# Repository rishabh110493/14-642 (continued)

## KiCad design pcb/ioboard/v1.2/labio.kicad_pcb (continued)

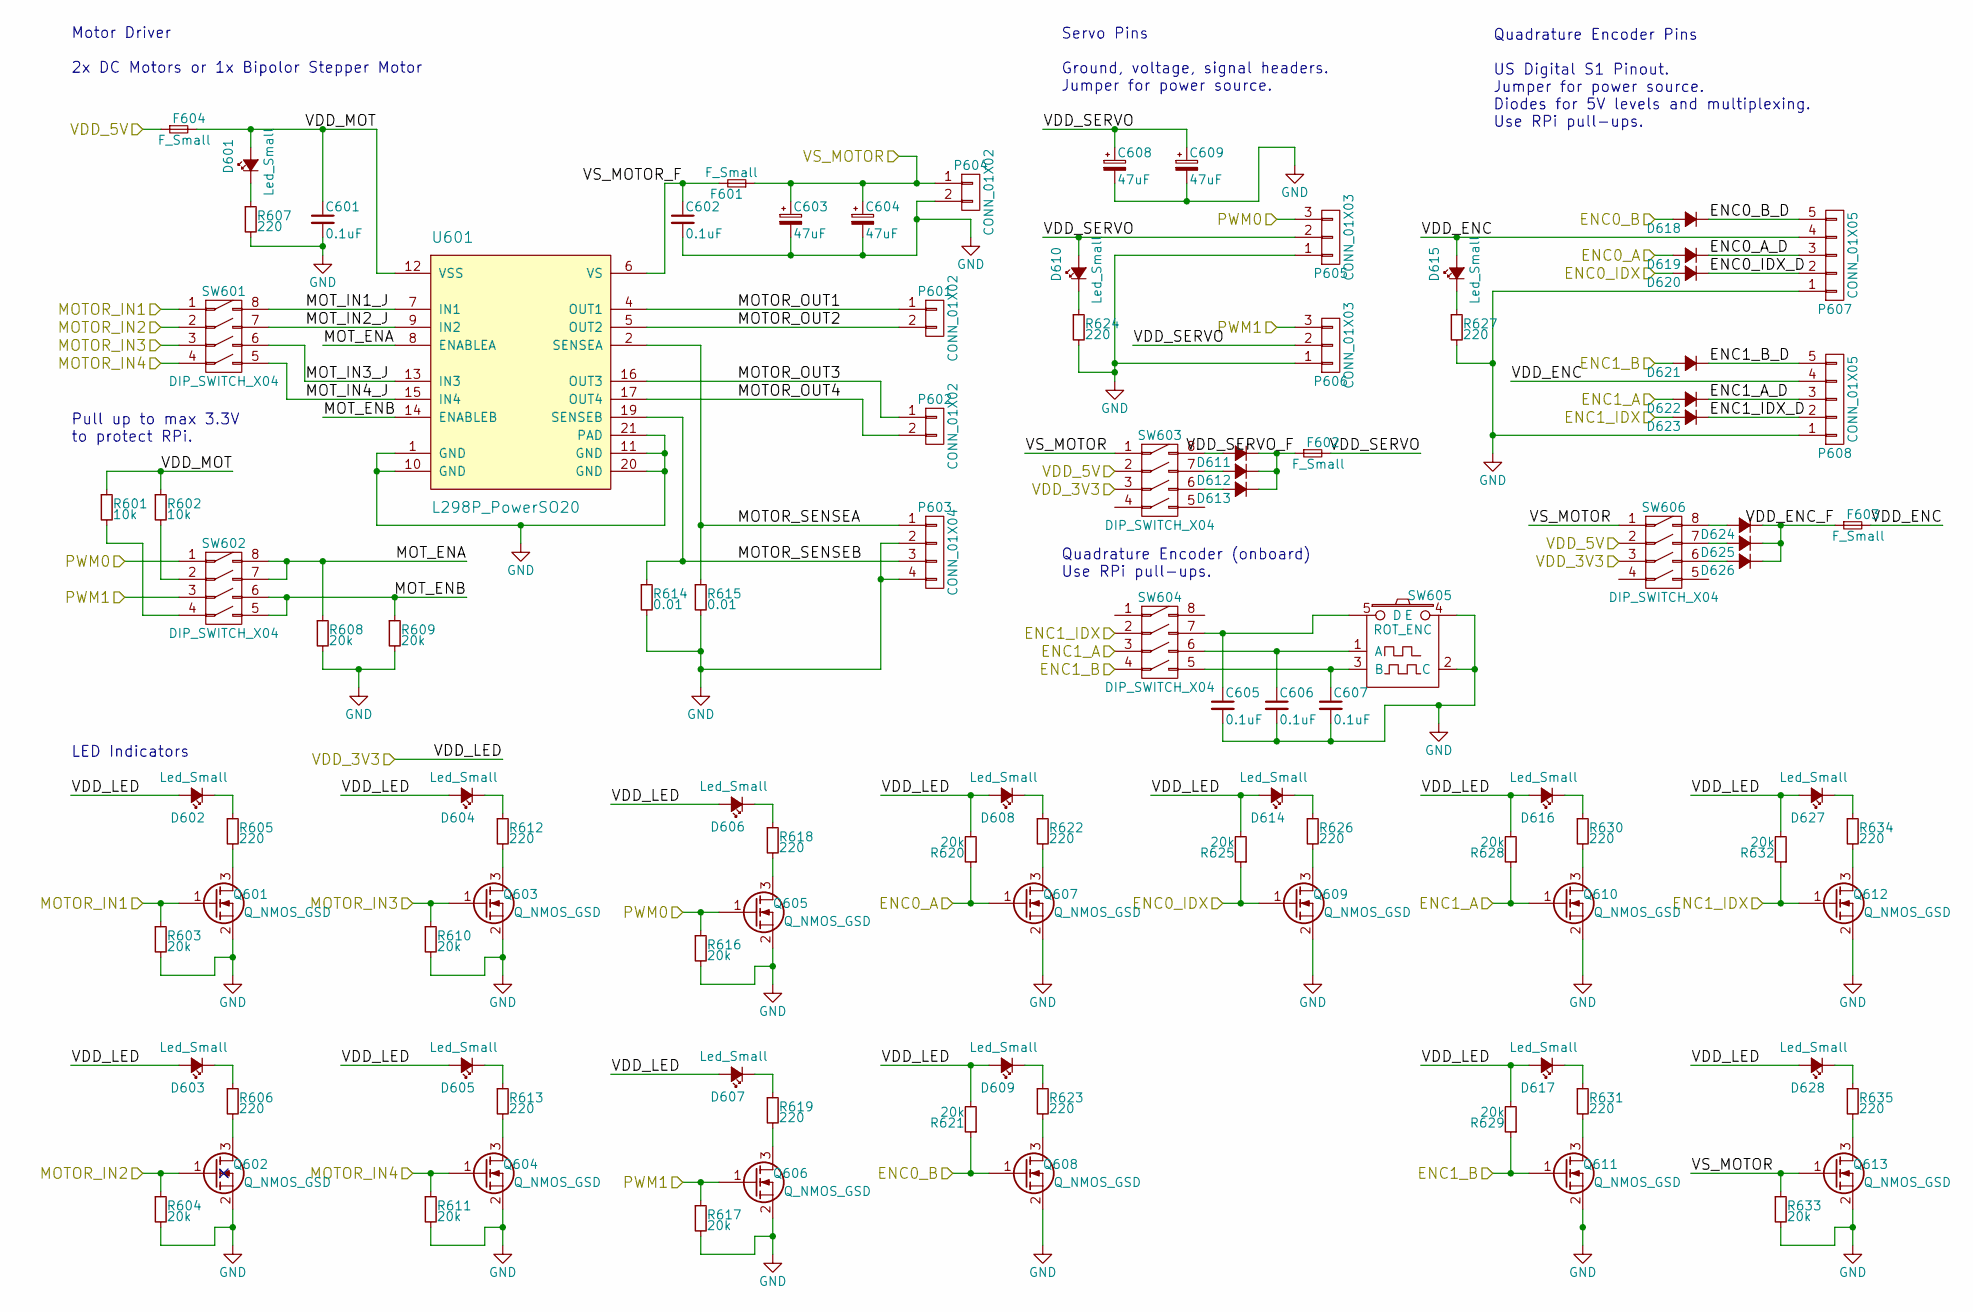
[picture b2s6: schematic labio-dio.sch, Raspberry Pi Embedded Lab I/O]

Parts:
C601, C602, C605, C606, C607: 0.1uF; C_0603
C603, C604, C608, C609: 47uF; c_elec_6.3x5.8
D601, D602, D603, D604, D605, D606, D607, D608, D609, D610, D614, D615, D616, D617, D627, D628: Led_Small; LED-0603
D611, D612, D613, D618, D619, D620, D621, D622, D623, D624, D625, D626: D_Small; SOD-523
F601: F_Small; OMNI-BLOCK_Fuse_10x5mm_Littelfuse
F602, F603, F604: F_Small; R_1206
P601, P602, P604: CONN_01X02; Pin_Header_Straight_1x02_Pitch3.5mm
P603: CONN_01X04; Pin_Header_Straight_1x04
P605, P606: CONN_01X03; Pin_Header_Straight_1x03
P607, P608: CONN_01X05; Pin_Header_Straight_1x05
Q601, Q602, Q603, Q604, Q605, Q606, Q607, Q608, Q609, Q610, Q611, Q612, Q613: Q_NMOS_GSD; SOT-23
R601, R602: 10k; R_0603
R603, R604, R608, R609, R610, R611, R616, R617, R620, R621, R625, R628, R629, R632, R633: 20k; R_0603
R605, R606, R607, R612, R613, R618, R619, R622, R623, R624, R626, R627, R630, R631, R634, R635: 220; R_0603
R614, R615: 0.01; R_1206
SW601, SW602, SW603, SW604, SW606: DIP_SWITCH_X04; DIP-8_W7.62mm_SMT
SW605: ROT_ENC; Rot-Enc-12mm-Horiz-Button
U601: L298P_PowerSO20; PowerSO20

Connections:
/3V3_EXTRA: D602.2 (A), D603.2 (A), D604.2 (A), D605.2 (A), D606.2 (A), D607.2 (A), D608.2 (A), D609.2 (A), D614.2 (A), D616.2 (A), D617.2 (A), D627.2 (A), D628.2 (A), R620.2, R621.2, R625.2, R628.2, R629.2, R632.2, SW603.3 (3A), SW606.3 (3A); also elsewhere on the board
/5V: F604.1, SW603.2 (2A), SW606.2 (2A); also elsewhere on the board
/I2C_INT: D619.2 (A), Q607.1 (G), R620.1; also elsewhere on the board
/I2S_BCLK: Q604.1 (G), R611.1, SW601.4 (4A); also elsewhere on the board
/I2S_LRCLK: Q603.1 (G), R610.1, SW601.3 (3A); also elsewhere on the board
/I2S_SDIN: Q601.1 (G), R603.1, SW601.1 (1A); also elsewhere on the board
/I2S_SDOUT: Q602.1 (G), R604.1, SW601.2 (2A); also elsewhere on the board
/PWM0: P605.3, Q605.1 (G), R616.1, SW602.1 (1A); also elsewhere on the board
/PWM1: P606.3, Q606.1 (G), R617.1, SW602.3 (3A); also elsewhere on the board
/labio-dio/ENC0_A_D: D619.1 (K), P607.3
/labio-dio/ENC0_B_D: D618.1 (K), P607.5
/labio-dio/ENC0_IDX_D: D620.1 (K), P607.2
/labio-dio/ENC1_A_D: D622.1 (K), P608.3
/labio-dio/ENC1_B_D: D621.1 (K), P608.5
/labio-dio/ENC1_IDX_D: D623.1 (K), P608.2
/labio-dio/MOTOR_OUT1: P601.1, U601.4 (OUT1)
/labio-dio/MOTOR_OUT2: P601.2, U601.5 (OUT2)
/labio-dio/MOTOR_OUT3: P602.1, U601.16 (OUT3)
/labio-dio/MOTOR_OUT4: P602.2, U601.17 (OUT4)
/labio-dio/MOTOR_SENSEA: P603.1, R615.1, U601.2 (SENSEA)
/labio-dio/MOTOR_SENSEB: P603.3, R614.1, U601.19 (SENSEB)
/labio-dio/MOT_ENA: R608.1, SW602.7 (2A), SW602.8 (1B), U601.8 (ENABLEA)
/labio-dio/MOT_ENB: R609.1, SW602.5 (4B), SW602.6 (3B), U601.14 (ENABLEB)
/labio-dio/MOT_IN1_J: SW601.8 (1B), U601.7 (IN1)
/labio-dio/MOT_IN2_J: SW601.7 (2A), U601.9 (IN2)
/labio-dio/MOT_IN3_J: SW601.6 (3B), U601.13 (IN3)
/labio-dio/MOT_IN4_J: SW601.5 (4B), U601.15 (IN4)
/labio-dio/VDD_ENC: D615.2 (A), F603.2, P607.4, P608.4
/labio-dio/VDD_ENC_F: D624.1 (K), D625.1 (K), D626.1 (K), F603.1
/labio-dio/VDD_MOT: C601.1, D601.2 (A), F604.2, R601.1, R602.1, U601.12 (VSS)
/labio-dio/VDD_SERVO: C608.1, C609.1, D610.2 (A), F602.2, P605.2, P606.2
/labio-dio/VDD_SERVO_F: D611.1 (K), D612.1 (K), D613.1 (K), F602.1
/labio-dio/VS_MOTOR: C603.1, C604.1, F601.1, P604.1, Q613.1 (G), R633.1, SW603.1 (1A), SW606.1 (1A); also elsewhere on the board
/labio-dio/VS_MOTOR_F: C602.1, F601.2, U601.6 (VS)
/labio-dpad/DPAD_CENTER: D622.2 (A), Q610.1 (G), R628.1, SW604.3 (3A); also elsewhere on the board
/labio-dpad/DPAD_DOWN: D623.2 (A), Q612.1 (G), R632.1, SW604.2 (2A); also elsewhere on the board
/labio-dpad/DPAD_LEFT: D618.2 (A), Q608.1 (G), R621.1; also elsewhere on the board
/labio-dpad/DPAD_RIGHT: D621.2 (A), Q611.1 (G), R629.1, SW604.4 (4A); also elsewhere on the board
/labio-dpad/DPAD_UP: D620.2 (A), Q609.1 (G), R625.1; also elsewhere on the board
GND: C601.2, C602.2, C603.2, C604.2, C605.2, C606.2, C607.2, C608.2, C609.2, P603.2, P603.4, P604.2, P605.1, P606.1, P607.1, P608.1, Q601.2 (S), Q602.2 (S), Q603.2 (S), Q604.2 (S), Q605.2 (S), Q606.2 (S), Q607.2 (S), Q608.2 (S), Q609.2 (S), Q610.2 (S), Q611.2 (S), Q612.2 (S), Q613.2 (S), R603.2, R604.2, R607.2, R608.2, R609.2, R610.2, R611.2, R614.2, R615.2, R616.2, R617.2, R624.2, R627.2, R633.2, SW605.2 (C), SW605.4 (E), U601.1 (GND), U601.10 (GND), U601.11 (GND), U601.20 (GND), U601.21 (PAD); also elsewhere on the board
unnamed: C605.1, SW604.7 (2A), SW605.5 (D)
unnamed: C606.1, SW604.6 (3B), SW605.1 (A)
unnamed: C607.1, SW604.5 (4B), SW605.3 (B)
unnamed: D601.1 (K), R607.1
unnamed: D602.1 (K), R605.1
unnamed: D603.1 (K), R606.1
unnamed: D604.1 (K), R612.1
unnamed: D605.1 (K), R613.1
unnamed: D606.1 (K), R618.1
unnamed: D607.1 (K), R619.1
unnamed: D608.1 (K), R622.1
unnamed: D609.1 (K), R623.1
unnamed: D610.1 (K), R624.1
unnamed: D611.2 (A), SW603.8 (1B)
unnamed: D612.2 (A), SW603.7 (2A)
unnamed: D613.2 (A), SW603.6 (3B)
unnamed: D614.1 (K), R626.1
unnamed: D615.1 (K), R627.1
unnamed: D616.1 (K), R630.1
unnamed: D617.1 (K), R631.1
unnamed: D624.2 (A), SW606.8 (1B)
unnamed: D625.2 (A), SW606.7 (2A)
unnamed: D626.2 (A), SW606.6 (3B)
unnamed: D627.1 (K), R634.1
unnamed: D628.1 (K), R635.1
unnamed: Q601.3 (D), R605.2
unnamed: Q602.3 (D), R606.2
unnamed: Q603.3 (D), R612.2
unnamed: Q604.3 (D), R613.2
unnamed: Q605.3 (D), R618.2
unnamed: Q606.3 (D), R619.2
unnamed: Q607.3 (D), R622.2
unnamed: Q608.3 (D), R623.2
unnamed: Q609.3 (D), R626.2
unnamed: Q610.3 (D), R630.2
unnamed: Q611.3 (D), R631.2
unnamed: Q612.3 (D), R634.2
unnamed: Q613.3 (D), R635.2
unnamed: R601.2, SW602.4 (4A)
unnamed: R602.2, SW602.2 (2A)

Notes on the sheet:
Quadrature Encoder Pins US Digital S1 Pinout. Jumper for power source. Diodes for 5V levels and multiplexing. Use RPi pull-ups.
Servo Pins Ground, voltage, signal headers. Jumper for power source.
Motor Driver 2x DC Motors or 1x Bipolor Stepper Motor
LED Indicators
Quadrature Encoder (onboard) Use RPi pull-ups.
Pull up to max 3.3V to protect RPi.

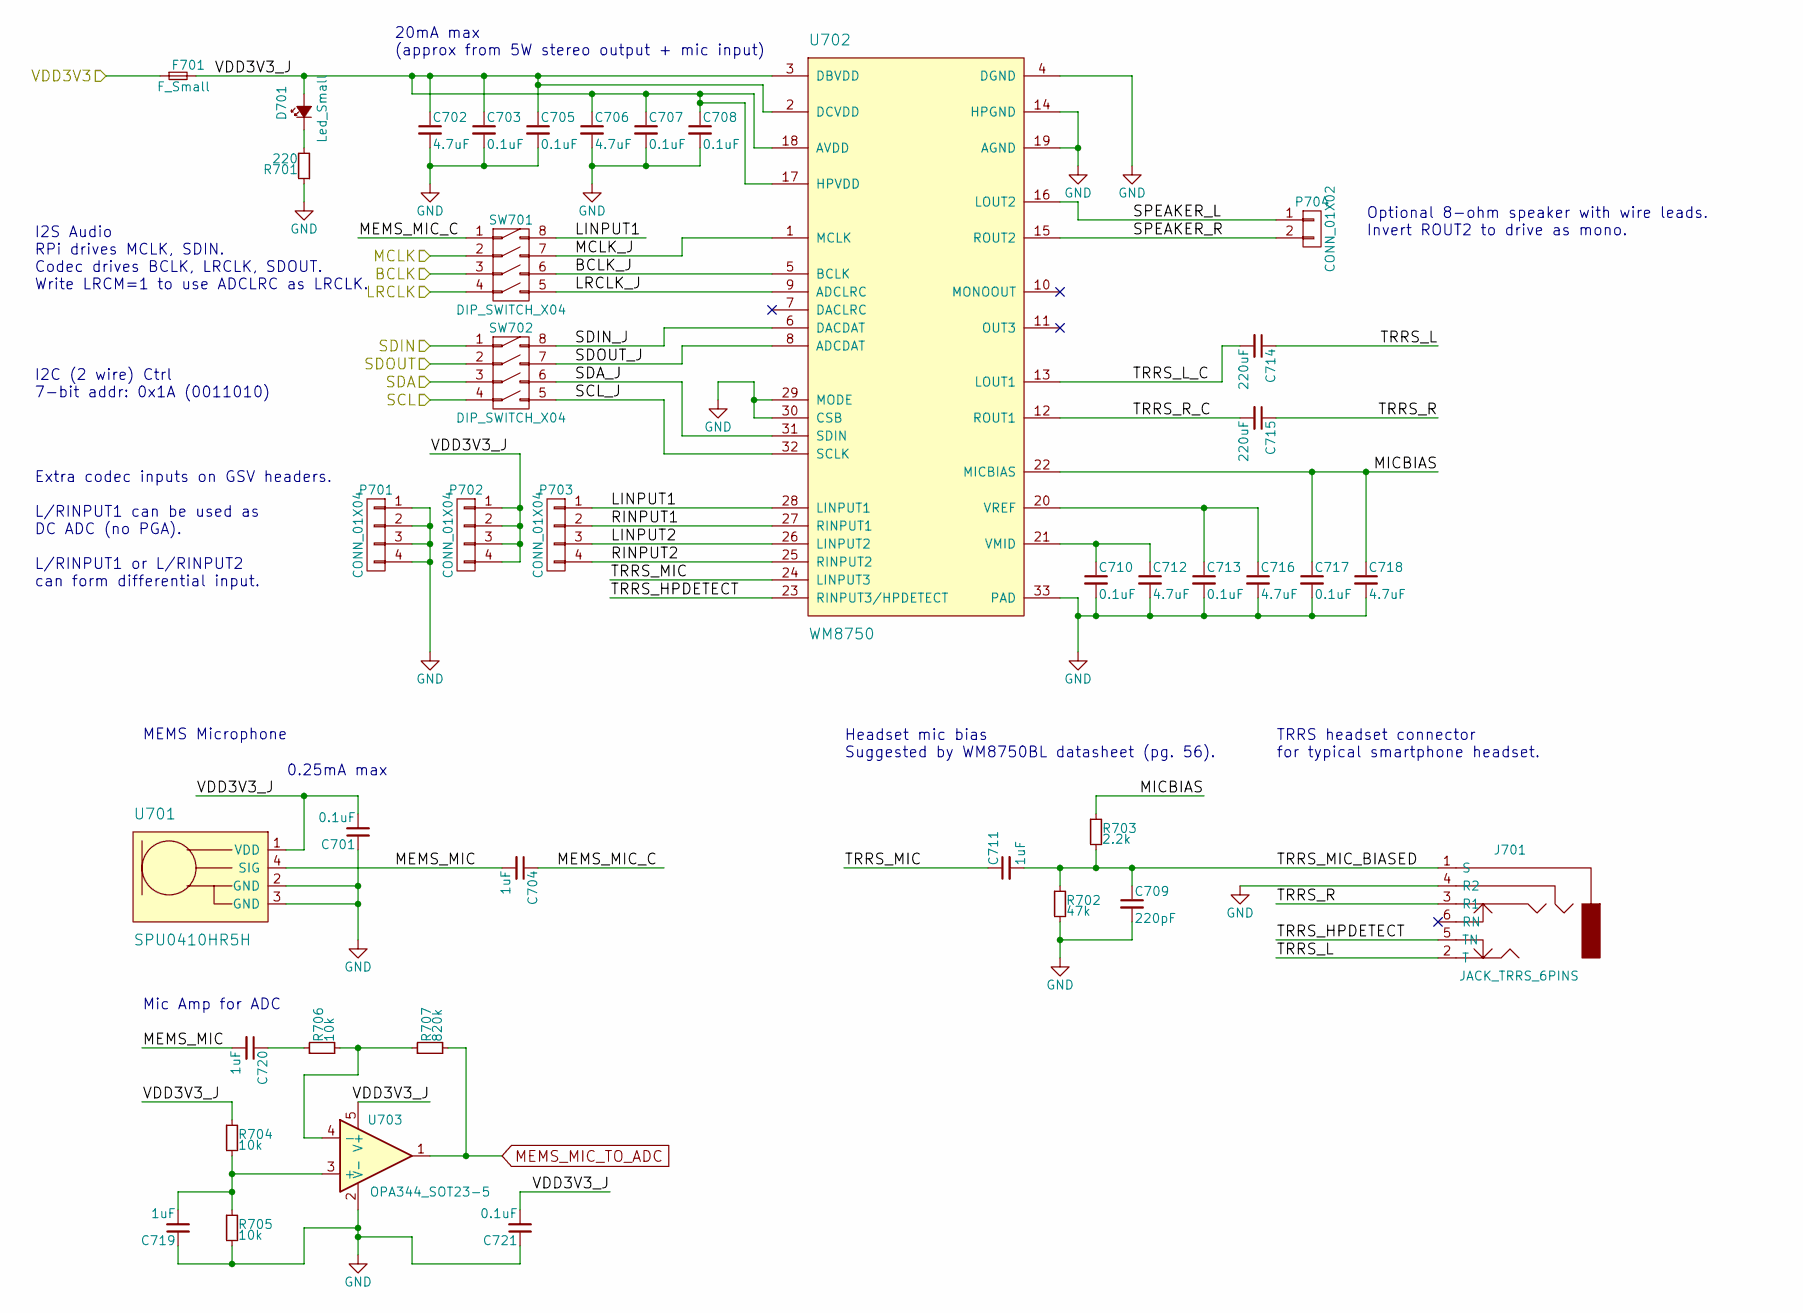
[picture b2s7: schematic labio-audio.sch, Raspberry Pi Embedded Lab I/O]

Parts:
C701, C703, C705, C707, C708, C710, C713, C717, C721: 0.1uF; C_0603
C702, C706, C712, C716, C718: 4.7uF; C_0805
C704, C711, C719, C720: 1uF; C_0603
C709: 220pF; C_0603
C714, C715: 220uF; C_1210
D701: Led_Small; LED-0603
F701: F_Small; R_1206
J701: JACK_TRRS_6PINS; 3.5mm-Jack-CUI-SJ-4351X
P701, P702, P703: CONN_01X04; Pin_Header_Straight_1x04
P704: CONN_01X02; Pin_Header_Straight_1x02
R701: 220; R_0603
R702: 47k; R_0603
R703: 2.2k; R_0603
R704, R705, R706: 10k; R_0603
R707: 820k; R_0603
SW701, SW702: DIP_SWITCH_X04; DIP-8_W7.62mm_SMT
U701: SPU0410HR5H
U702: WM8750; QFN-32-1EP_5x5mm_Pitch0.5mm
U703: OPA344_SOT23-5; SOT-23-5

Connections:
/3V3_EXTRA: F701.1; also elsewhere on the board
/GPCLK1: SW701.2 (2A); also elsewhere on the board
/I2C_SCL: SW702.4 (4A); also elsewhere on the board
/I2C_SDA: SW702.3 (3A); also elsewhere on the board
/I2S_BCLK: SW701.3 (3A); also elsewhere on the board
/I2S_LRCLK: SW701.4 (4A); also elsewhere on the board
/I2S_SDIN: SW702.1 (1A); also elsewhere on the board
/I2S_SDOUT: SW702.2 (2A); also elsewhere on the board
/labio-audio/BCLK_J: SW701.6 (3B), U702.5 (BCLK)
/labio-audio/LINPUT1: P703.1, SW701.8 (1B), U702.28 (LINPUT1)
/labio-audio/LINPUT2: P703.3, U702.26 (LINPUT2)
/labio-audio/LRCLK_J: SW701.5 (4B), U702.9 (ADCLRC)
/labio-audio/MCLK_J: SW701.7 (2A), U702.1 (MCLK)
/labio-audio/MEMS_MIC: C704.2, C720.2, U701.4 (SIG)
/labio-audio/MEMS_MIC_C: C704.1, SW701.1 (1A)
/labio-audio/MICBIAS: C717.1, C718.1, R703.1, U702.22 (MICBIAS)
/labio-audio/RINPUT1: P703.2, U702.27 (RINPUT1)
/labio-audio/RINPUT2: P703.4, U702.25 (RINPUT2)
/labio-audio/SCL_J: SW702.5 (4B), U702.32 (SCLK)
/labio-audio/SDA_J: SW702.6 (3B), U702.31 (SDIN)
/labio-audio/SDIN_J: SW702.8 (1B), U702.6 (DACDAT)
/labio-audio/SDOUT_J: SW702.7 (2A), U702.8 (ADCDAT)
/labio-audio/SPEAKER_L: P704.1, U702.16 (LOUT2)
/labio-audio/SPEAKER_R: P704.2, U702.15 (ROUT2)
/labio-audio/TRRS_HPDETECT: J701.5 (TN), U702.23 (RINPUT3/HPDETECT)
/labio-audio/TRRS_L: C714.1, J701.2 (T)
/labio-audio/TRRS_L_C: C714.2, U702.13 (LOUT1)
/labio-audio/TRRS_MIC: C711.1, U702.24 (LINPUT3)
/labio-audio/TRRS_MIC_BIASED: C709.1, C711.2, J701.1 (S), R702.1, R703.2
/labio-audio/TRRS_R: C715.1, J701.3 (R1)
/labio-audio/TRRS_R_C: C715.2, U702.12 (ROUT1)
/labio-audio/VDD3V3_J: C701.2, C702.1, C703.1, C705.1, C706.1, C707.1, C708.1, C721.2, D701.2 (A), F701.2, P702.1, P702.2, P702.3, P702.4, R704.1, U701.1 (VDD), U702.2 (DCVDD), U702.3 (DBVDD), U702.17 (HPVDD), U702.18 (AVDD), U703.5 (V+)
GND: C701.1, C702.2, C703.2, C705.2, C706.2, C707.2, C708.2, C709.2, C710.2, C712.2, C713.2, C716.2, C717.2, C718.2, C719.1, C721.1, J701.4 (R2), P701.1, P701.2, P701.3, P701.4, R701.1, R702.2, R705.2, U701.2 (GND), U701.3 (GND), U702.4 (DGND), U702.14 (HPGND), U702.19 (AGND), U702.29 (MODE), U702.30 (CSB), U702.33 (PAD), U703.2 (V-); also elsewhere on the board
MEMS_MIC_TO_ADC: R707.2, U703.1; also elsewhere on the board
unnamed: C710.1, C712.1, U702.21 (VMID)
unnamed: C713.1, C716.1, U702.20 (VREF)
unnamed: C719.2, R704.2, R705.1, U703.3 (+)
unnamed: C720.1, R706.1
unnamed: D701.1 (K), R701.2
unnamed: R706.2, R707.1, U703.4 (-)

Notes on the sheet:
Optional 8-ohm speaker with wire leads. Invert ROUT2 to drive as mono.
MEMS Microphone
Extra codec inputs on GSV headers. L/RINPUT1 can be used as DC ADC (no PGA). L/RINPUT1 or L/RINPUT2 can form differential input.
TRRS headset connector for typical smartphone headset.
I2S Audio RPi drives MCLK, SDIN. Codec drives BCLK, LRCLK, SDOUT. Write LRCM=1 to use ADCLRC as LRCLK.
I2C (2 wire) Ctrl 7-bit addr: 0x1A (0011010)
Headset mic bias Suggested by WM8750BL datasheet (pg. 56).
0.25mA max
20mA max (approx from 5W stereo output + mic input)
Mic Amp for ADC

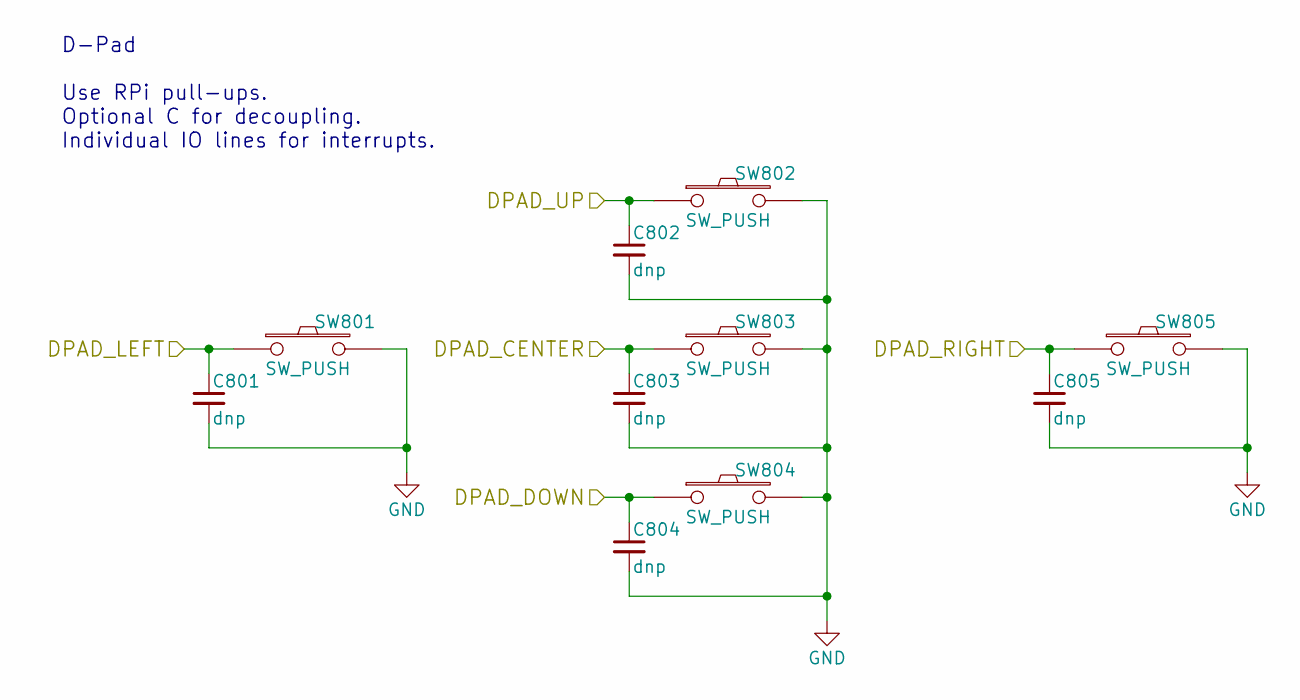
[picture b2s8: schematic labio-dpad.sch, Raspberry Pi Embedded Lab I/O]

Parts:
C801, C802, C803, C804, C805: dnp; C_0603
SW801, SW802, SW803, SW804, SW805: SW_PUSH; SW_SPST_EVPBF

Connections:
/labio-dpad/DPAD_CENTER: C803.1, SW803.1; also elsewhere on the board
/labio-dpad/DPAD_DOWN: C804.1, SW804.1; also elsewhere on the board
/labio-dpad/DPAD_LEFT: C801.1, SW801.1; also elsewhere on the board
/labio-dpad/DPAD_RIGHT: C805.1, SW805.1; also elsewhere on the board
/labio-dpad/DPAD_UP: C802.1, SW802.1; also elsewhere on the board
GND: C801.2, C802.2, C803.2, C804.2, C805.2, SW801.2, SW802.2, SW803.2, SW804.2, SW805.2; also elsewhere on the board

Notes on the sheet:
D-Pad Use RPi pull-ups. Optional C for decoupling. Individual IO lines for interrupts.

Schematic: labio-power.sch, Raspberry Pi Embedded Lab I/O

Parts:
P901: CONN_01X06; Pin_Header_Angled_1x06

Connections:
/5V: P901.6; also elsewhere on the board
/labio-dio/VS_MOTOR: P901.1, P901.2; also elsewhere on the board
GND: P901.3, P901.4; also elsewhere on the board

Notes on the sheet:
External Power (Future) Provides logic and motor power from power supply or battery pack with possible charging from USB (rpi) power. 2x motor power for current rating.

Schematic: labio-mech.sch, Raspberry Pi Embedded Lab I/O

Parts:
G1: CMU_LOGO; cmu_logo_fsilk_3.7mm
G2: WISE_LOGO; wise_logo_fsilk_2.5mm
G3: CMU_LOGO; cmu_logo_fcu_3.7mm
G4: WISE_LOGO; wise_logo_fcu_2.5mm
H1001, H1002, H1003, H1004, H1005, H1006, H1007, H1008, H1009: hole; hole-m3

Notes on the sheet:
RPi-like Mounting Holes M3 for M3/no 4/M2.5 hardware.
Heatsink Mounting 25x25mm with 30x30mm M3 holes

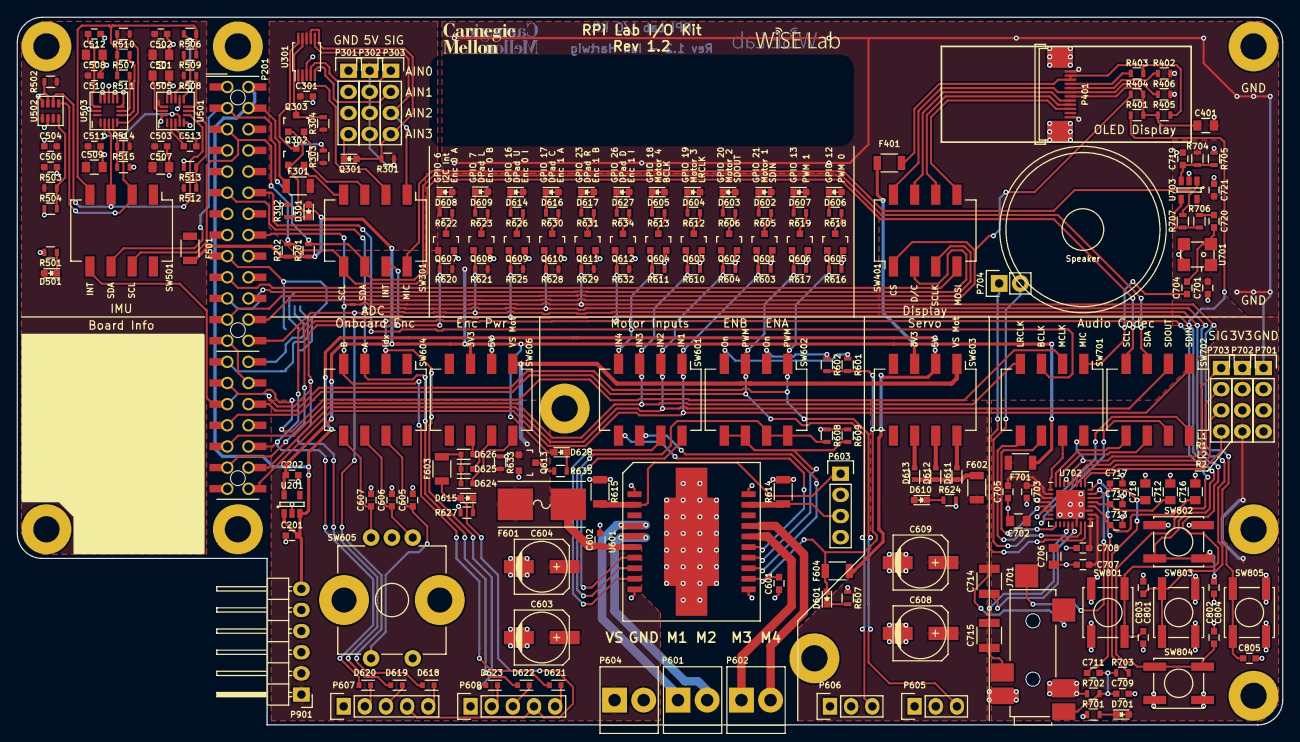
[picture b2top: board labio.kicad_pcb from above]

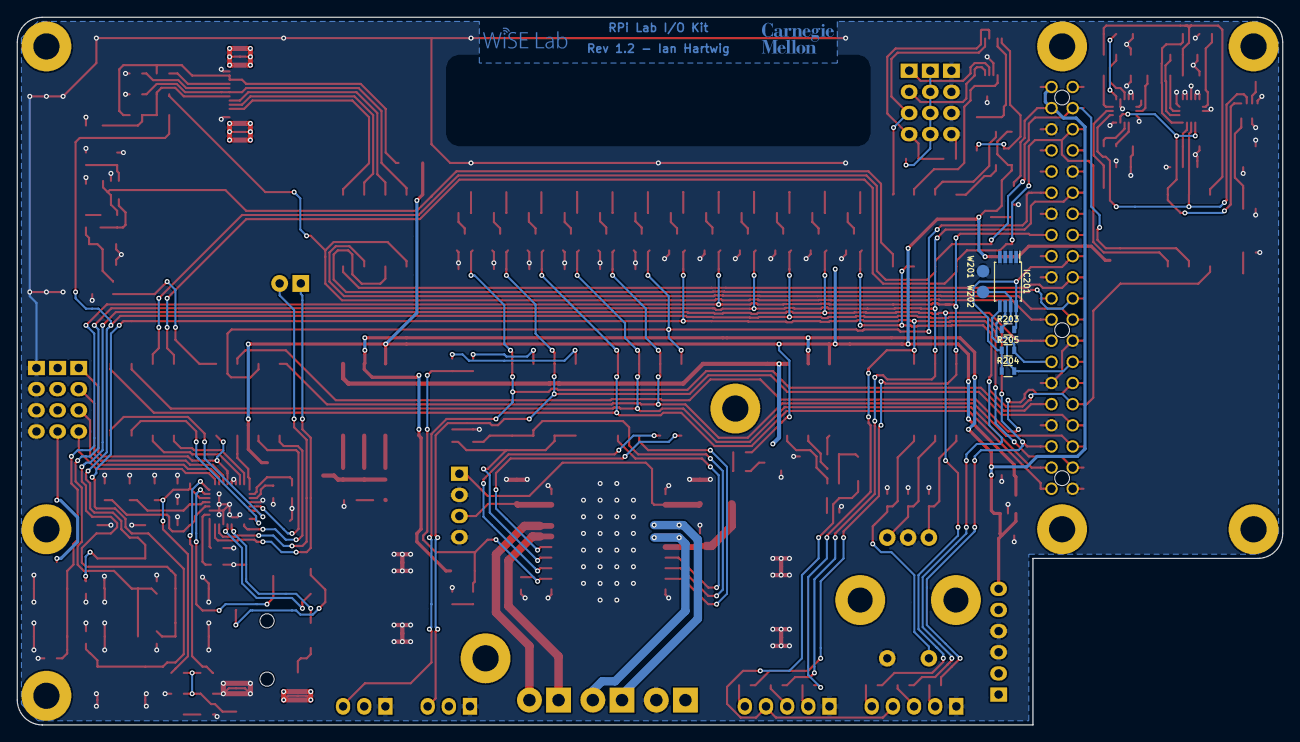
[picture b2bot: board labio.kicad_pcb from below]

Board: 2 copper layers, 152.0 x 85.0 mm, 238 parts (8 on the bottom side), 160 nets.

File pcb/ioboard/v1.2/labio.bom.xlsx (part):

Source | /Users/ihartwig/repos/rpi-labio/pcb/labio.sch
Kicad Rev | Eeschema 4.0.0-stable
Generated Date | Monday July 25 2016 'PMt' 11:51:32 PM
Title | Raspberry Pi Embedded Lab I/O
Company | Carnegie Mellon University
Revision | 1.2
Date Issue | 42606
Reference | Value | Footprint | Qty | Type | Mfg | Mfg Part No | Description | Digikey Part No | Comments
C201, C202, C301, C502, C503, C504, C506, C510, C511, C601, C602, C605, C606, C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 | 0.1uF | Capacitors_SMD:C_0603 | 23 | SMT | Murata | GRM188R71C104KA01D | CAP CER 0.1uF ±10% 16V X7R 0603
C401 | dnp-4.7uF | Capacitors_SMD:C_0805 | 1 | DNS | Samsung | CL21A475KPFNNNG | 4.7µF 10V Ceramic Capacitor X5R 0805 | 1276-6464-1-ND | http://www.digikey.com/product-detail/en/samsung-electro-mec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
C501, C505, C507, C508, C509, C702, C706, C712, C716, C718 | 4.7uF | Capacitors_SMD:C_0805 | 10 | SMT | Samsung | CL21A475KPFNNNG | 4.7µF 10V Ceramic Capacitor X5R 0805 | 1276-6464-1-ND | http://www.digikey.com/product-detail/en/samsung-electro-mec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
C512 | 0.01uF-25V | Capacitors_SMD:C_0603 | 1 | SMT | Murata | GRM188R71H103KA01D | CAP CER 0.01uF ±10% 50V X7R 0603
C513 | 0.22uF | Capacitors_SMD:C_0603 | 1 | SMT | Murata | GRM188R71C224KA01D | CAP CER 0.22UF ±10% 16V X7R 0603
C603, C604, C608, C609 | 47uF | Capacitors_SMD:c_elec_6.3x5.8 | 4 | SMT | Nichicon | UWR1E470MCL1GB | 47µF 25V Aluminum Capacitors Radial, Can - SMD 2000 Hrs @ 85°C | 493-14562-1-ND | http://www.digikey.com/product-detail/en/nichicon/UWR1E470MC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
C709 | 220pF | Capacitors_SMD:C_0603 | 1 | SMT | Murata | GRM188R71H221KA01D | CAP CER 220PF ±10% 50V X7R 0603
C704, C711, C719, C720 | 1uF | Capacitors_SMD:C_0603 | 4 | SMT | Samsung | CL10B105KP8NNNC | 1µF 10V Ceramic Capacitor X7R 0603 (1608 Metric) 0.063" L x 0.031" W (1.60mm x 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 | 1276-1946-1-ND | http://www.digikey.com/product-detail/en/samsung-electro-mec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
C714, C715 | 220uF | Capacitors_SMD:C_1210 | 2 | SMT | Samsung | CL32A227MQVNNNE | 220µF 6.3V Ceramic Capacitor X5R 1210 | 1276-3375-1-ND | http://www.digikey.com/product-detail/en/samsung-electro-mec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
C801, C802, C803, C804, C805 | dnp | Capacitors_SMD:C_0603 | 5 | DNS
D301, D501, D601, D602, D603, D604, D605, D606, D607, D608, D609, D610, D614, D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 | Led_Small | LEDs:LED-0603 | 19 | SMT | Lite-On | LTST-C190GKT | LED GREEN CLEAR 0603 SMD | 160-1183-1-ND | http://www.digikey.com/product-detail/en/lite-on-inc/LTST-C1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
D611, D612, D613, D618, D619, D620, D621, D622, D623, D624, D625, D626 | D_Small | Diodes_SMD:SOD-523 | 12 | SMT | Panasonic | DB2S20500L | DIODE SCHOTTKY 15V 200MA SSMINI2 | DB2S20500LCT-ND | http://www.digikey.com/product-detail/en/panasonic-electroni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
F301, F401, F501, F603, F604, F701 | F_Small | Resistors_SMD:R_1206 | 6 | SMT | Bel Fuse | 0ZCJ0010FF2E | PTC RESTTBLE 0.10A 60V CHIP 1206 | 507-1794-1-ND | http://www.digikey.com/product-detail/en/bel-fuse-inc/0ZCJ00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
F601 | F_Small | labio-special:OMNI-BLOCK_Fuse_10x5mm_Littelfuse | 1 | SMT | Littelfuse | 0154004.DRT | FUSE BRD MNT 4A 125VAC/VDC 2SMD | F1309CT-ND | http://www.digikey.com/product-detail/en/littelfuse-inc/0154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
F602 | F_Small | Resistors_SMD:R_1206 | 1 | SMT | Bel Fuse | 0ZCJ0050AF2E | PTC RESTTBLE 0.50A 24V CHIP 1206 | 507-1803-1-ND | http://www.digikey.com/product-detail/en/bel-fuse-inc/0ZCJ00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
G1 | CMU_LOGO | labio-special:cmu_logo_fsilk_3.7mm | 1 | DNS
G2 | WISE_LOGO | labio-special:wise_logo_fsilk_2.5mm | 1 | DNS
G3 | CMU_LOGO | labio-special:cmu_logo_fcu_3.7mm | 1 | DNS
G4 | WISE_LOGO | labio-special:wise_logo_fcu_2.5mm | 1 | DNS
H1001, H1002, H1003, H1004, H1005, H1006, H1007, H1008, H1009 | hole | labio-special:hole-m3 | 9 | DNS
IC201 | AT24CS32-XHM | Housings_SSOP:TSSOP-8_4.4x3mm_Pitch0.65mm | 1 | DNS
J701 | JACK_TRRS_6PINS | labio-special:3.5mm-Jack-CUI-SJ-4351X | 1 | SMT | CUI Inc | SJ-43515RS-SMT-TR | 3.50mm (0.141", 1/8", Mini Plug) - Headphone Phone Jack Multiple Connector Sold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 | CP-43515RSSJCT-ND | http://www.digikey.com/product-detail/en/cui-inc/SJ-43515RS-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
P201 | CONN_02X20 | labio-special:Pin_Header_Straight_TH-SMT-NoPaste_2x20 | 1 | DNS
P301, P302, P303, P603, P701, P702, P703 | CONN_01X04 | Pin_Headers:Pin_Header_Straight_1x04 | 7 | TH | Harwin, Inc. | M20-9990446 | 4 Positions Header, Unshrouded, Breakaway Connector 0.100" (2.54mm) Through Hol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 | 952-2266-ND | http://www.digikey.com/product-detail/en/harwin-inc/M20-9990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
P401 | SFV12R-1ST__HLF | labio-special:SFVxxR-xSTxxHLF | 1 | SMT | Amphenol FCI | SFV12R-3STBE1HLF | 12 Position FPC Connector Contacts, Bottom 0.020" (0.50mm) Surface Mount, Right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 | 609-5196-1-ND | Could also use SFV12R-1STE1HLF. http://www.digikey.com/product-detail/en/amphen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
P601, P602, P604 | CONN_01X02 | labio-special:Pin_Header_Straight_1x02_Pitch3.5mm | 1 | TH | On Shore Technology, Inc. | OSTTE020104 | 2 Position Wire to Board Terminal Block Horizontal with Board 0.138" (3.50mm) T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 | ED2740-ND | http://www.digikey.com/product-detail/en/on-shore-technology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
P605, P606 | CONN_01X03 | Pin_Headers:Pin_Header_Straight_1x03 | 2 | TH | Harwin, Inc. | M20-9990346 | 3 Positions Header, Unshrouded, Breakaway Connector 0.100" (2.54mm) Through Hol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 | 952-2264-ND | http://www.digikey.com/product-detail/en/harwin-inc/M20-9990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
P607, P608 | CONN_01X05 | Pin_Headers:Pin_Header_Straight_1x05 | 2 | TH | Harwin, Inc. | M20-9990546 | 5 Positions Header, Unshrouded, Breakaway Connector 0.100" (2.54mm) Through Hol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 | 952-2268-ND | http://www.digikey.com/product-detail/en/harwin-inc/M20-9990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
P704 | CONN_01X02 | Pin_Headers:Pin_Header_Straight_1x02 | 1 | DNS
P901 | CONN_01X06 | Pin_Headers:Pin_Header_Angled_1x06 | 1 | DNS
Q301 | PHOTOTRANSISTOR | LEDs:LED-0603 | 1 | SMT | Everlight Electronics | PT19-21B/L41/TR8 | PHOTOTRANSISTOR FLAT BK MINI SMD | 1080-1383-1-ND | http://www.digikey.com/product-detail/en/everlight-electroni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
Q302, Q303, Q601, Q602, Q603, Q604, Q605, Q606, Q607, Q608, Q609, Q610, Q611, Q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 | Q_NMOS_GSD | TO_SOT_Packages_SMD:SOT-23 | 15 | SMT | ON Semiconductor | NTR5103NT1G | MOSFET N-CH 60V 0.26A SOT23 | NTR5103NT1GOSCT-ND | http://www.digikey.com/product-detail/en/on-semiconductor/NT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
R201, R202, R301, R703 | 2.2k | Resistors_SMD:R_0603 | 4 | SMT | Vishay Dale | CRCW06032K20FKEA | RES SMD 2.2K OHM 1% 1/10W 0603
R203 | dnp-10k | Resistors_SMD:R_0603 | 1 | DNS
R204, R205 | dnp-3.9k | Resistors_SMD:R_0603 | 2 | DNS
R302, R501, R605, R606, R607, R612, R613, R618, R619, R622, R623, R624, R626, R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 | 220 | Resistors_SMD:R_0603 | 19 | SMT | Vishay Dale | CRCW0603220RFKEA | RES SMD 220 OHM 1% 1/10W 0603
R303, R304, R601, R602, R704, R705, R706 | 10k | Resistors_SMD:R_0603 | 7 | SMT | Vishay Dale | CRCW060310K0FKEA | RES SMD 10K OHM 1% 1/10W 0603
R401, R402, R403, R502, R504, R506, R507, R508, R509, R510, R511, R513, R515 | 0 | Resistors_SMD:R_0603 | 13 | SMT | Vishay Dale | CRCW06030000Z0EA | RES SMD 0.0OHM JUMPER 1/10W 0603
R404, R406, R503, R512, R514 | dnp-0 | Resistors_SMD:R_0603 | 5 | DNS | Vishay Dale | CRCW06030000Z0EA | RES SMD 0.0OHM JUMPER 1/10W 0603
R405 | dnp-47k | Resistors_SMD:R_0603 | 1 | DNS | Vishay Dale | CRCW060347K0FKEA | RES SMD 47K OHM 1% 1/10W 0603
R603, R604, R608, R609, R610, R611, R616, R617, R620, R621, R625, R628, R629, R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 | 20k | Resistors_SMD:R_0603 | 15 | SMT | Vishay Dale | CRCW060320K0FKEA | RES SMD 20K OHM 1% 1/10W 0603
R614, R615 | 0.01 | Resistors_SMD:R_1206 | 2 | SMT | Samsung | RUW3216FR100CS | RES SMD 0.1 OHM 1% 1W 1206 | 1276-6187-1-ND | http://www.digikey.com/product-detail/en/samsung-electro-mec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
R702 | 47k | Resistors_SMD:R_0603 | 1 | SMT | Vishay Dale | CRCW060347K0FKEA | RES SMD 47K OHM 1% 1/10W 0603
R707 | 820k | Resistors_SMD:R_0603 | 1 | SMT | Vishay Dale | CRCW0603820KFKEA | RES SMD 820K OHM 1% 1/10W 0603
SW301, SW401, SW501, SW601, SW602, SW603, SW604, SW606, SW701, SW702 | DIP_SWITCH_X04 | labio-special:DIP-8_W7.62mm_SMT | 10 | SMT | CTS Electrocomponents | 219-4MST | Dip Switch SPST 4 Position Surface Mount Slide (Standard) Actuator 100mA 20VDC | CT2194MST-ND | http://www.digikey.com/product-detail/en/cts-electrocomponen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

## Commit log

2017-06-19 work done in 14-642
